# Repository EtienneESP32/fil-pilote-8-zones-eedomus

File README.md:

# Contrôleur fil pilote 8 zones — eedomus / ESP32-S3

Projet de carte rail DIN destinée à piloter huit zones de chauffage par fil pilote, avec intégration locale eedomus par HTTP. La carte contrôleur retenue pour l'étude est le Waveshare ESP32-S3-POE-ETH, SKU 28771, avec option d'alimentation PoE et alimentation secteur isolée locale.

> **Attention — projet en cours de conception.** Le PCB EasyEDA généré par conversion est un brouillon non placé/routé et ne doit pas être commandé ou raccordé au secteur. Le schéma source contient encore l'ancienne architecture WT32-S1/MCP23017. Les distances d'isolement, les valeurs de composants, la topologie triphasée, le codage des six ordres et les protections ne sont pas validés. Toute réalisation secteur doit être revue par une personne qualifiée.

## État

- Cahier initial, PDF et JSON EasyEDA source archivés dans le dépôt.
- Dossier de documentation technique dans [`docs/`](docs/README.md).
- Copie de travail EasyEDA R1 créée dans le compte EasyEDA de l'utilisateur, distincte du projet source.
- PCB issu de conversion présent dans cette copie R1; placement, contour, routage, DRC et export de fabrication restent à faire.
- Le projet vise 8 sorties fil pilote, 6 ordres, phase `PHASE_PROT` unique retenue par l'utilisateur, Ethernet, eedomus et options PoE/alimentation locale.
- Une recherche de projets similaires met en évidence un conflit à résoudre : un projet triphasé comparable exige une phase pilote correspondant à la phase d'alimentation du radiateur.

## Documentation

- [Index de la documentation](docs/README.md)
- [Cahier des charges](docs/01_Cahier-des-charges.md)
- [Architecture et interfaces](docs/02_Architecture-et-interfaces.md)
- [Nomenclature prévisionnelle](docs/03_Nomenclature.md)
- [Note d'implantation PCB](docs/04_Implantation-PCB.md)
- [Firmware et exploitation](docs/05_Firmware-et-exploitation.md)
- [Plan de validation](docs/06_Plan-de-validation.md)
- [Questions/décisions ouvertes](docs/07_Questions-a-confirmer.md)
- [Revue du schéma source](docs/08_Revue-schema-source.md)
- [Commande directe des optos](docs/09_Commande-directe-opto.md)
- [Projets similaires](docs/10_Projets-similaires.md)

## Contenu source

- `contour du projet.docx` : cahier initial.
- `SCH_FilPilote_8Zones_DIN_2_2026-11-06.json` : export EasyEDA source, ancienne version.
- `Schematic_FilPilote_8Zones_DIN_2_2026-11-06.pdf` : export PDF de cette source, obsolète par rapport aux choix R1.
- `Analyse et commentaires.md` : revue initiale et décisions ultérieures.

## Sauvegarde GitHub

La publication distante n'est pas encore effectuée. Recommandation : créer un dépôt **privé** au départ, vérifier les fichiers inclus et ne le rendre public qu'après revue sécurité/documentation. Voir [`GITHUB_PUBLISHING.md`](GITHUB_PUBLISHING.md).

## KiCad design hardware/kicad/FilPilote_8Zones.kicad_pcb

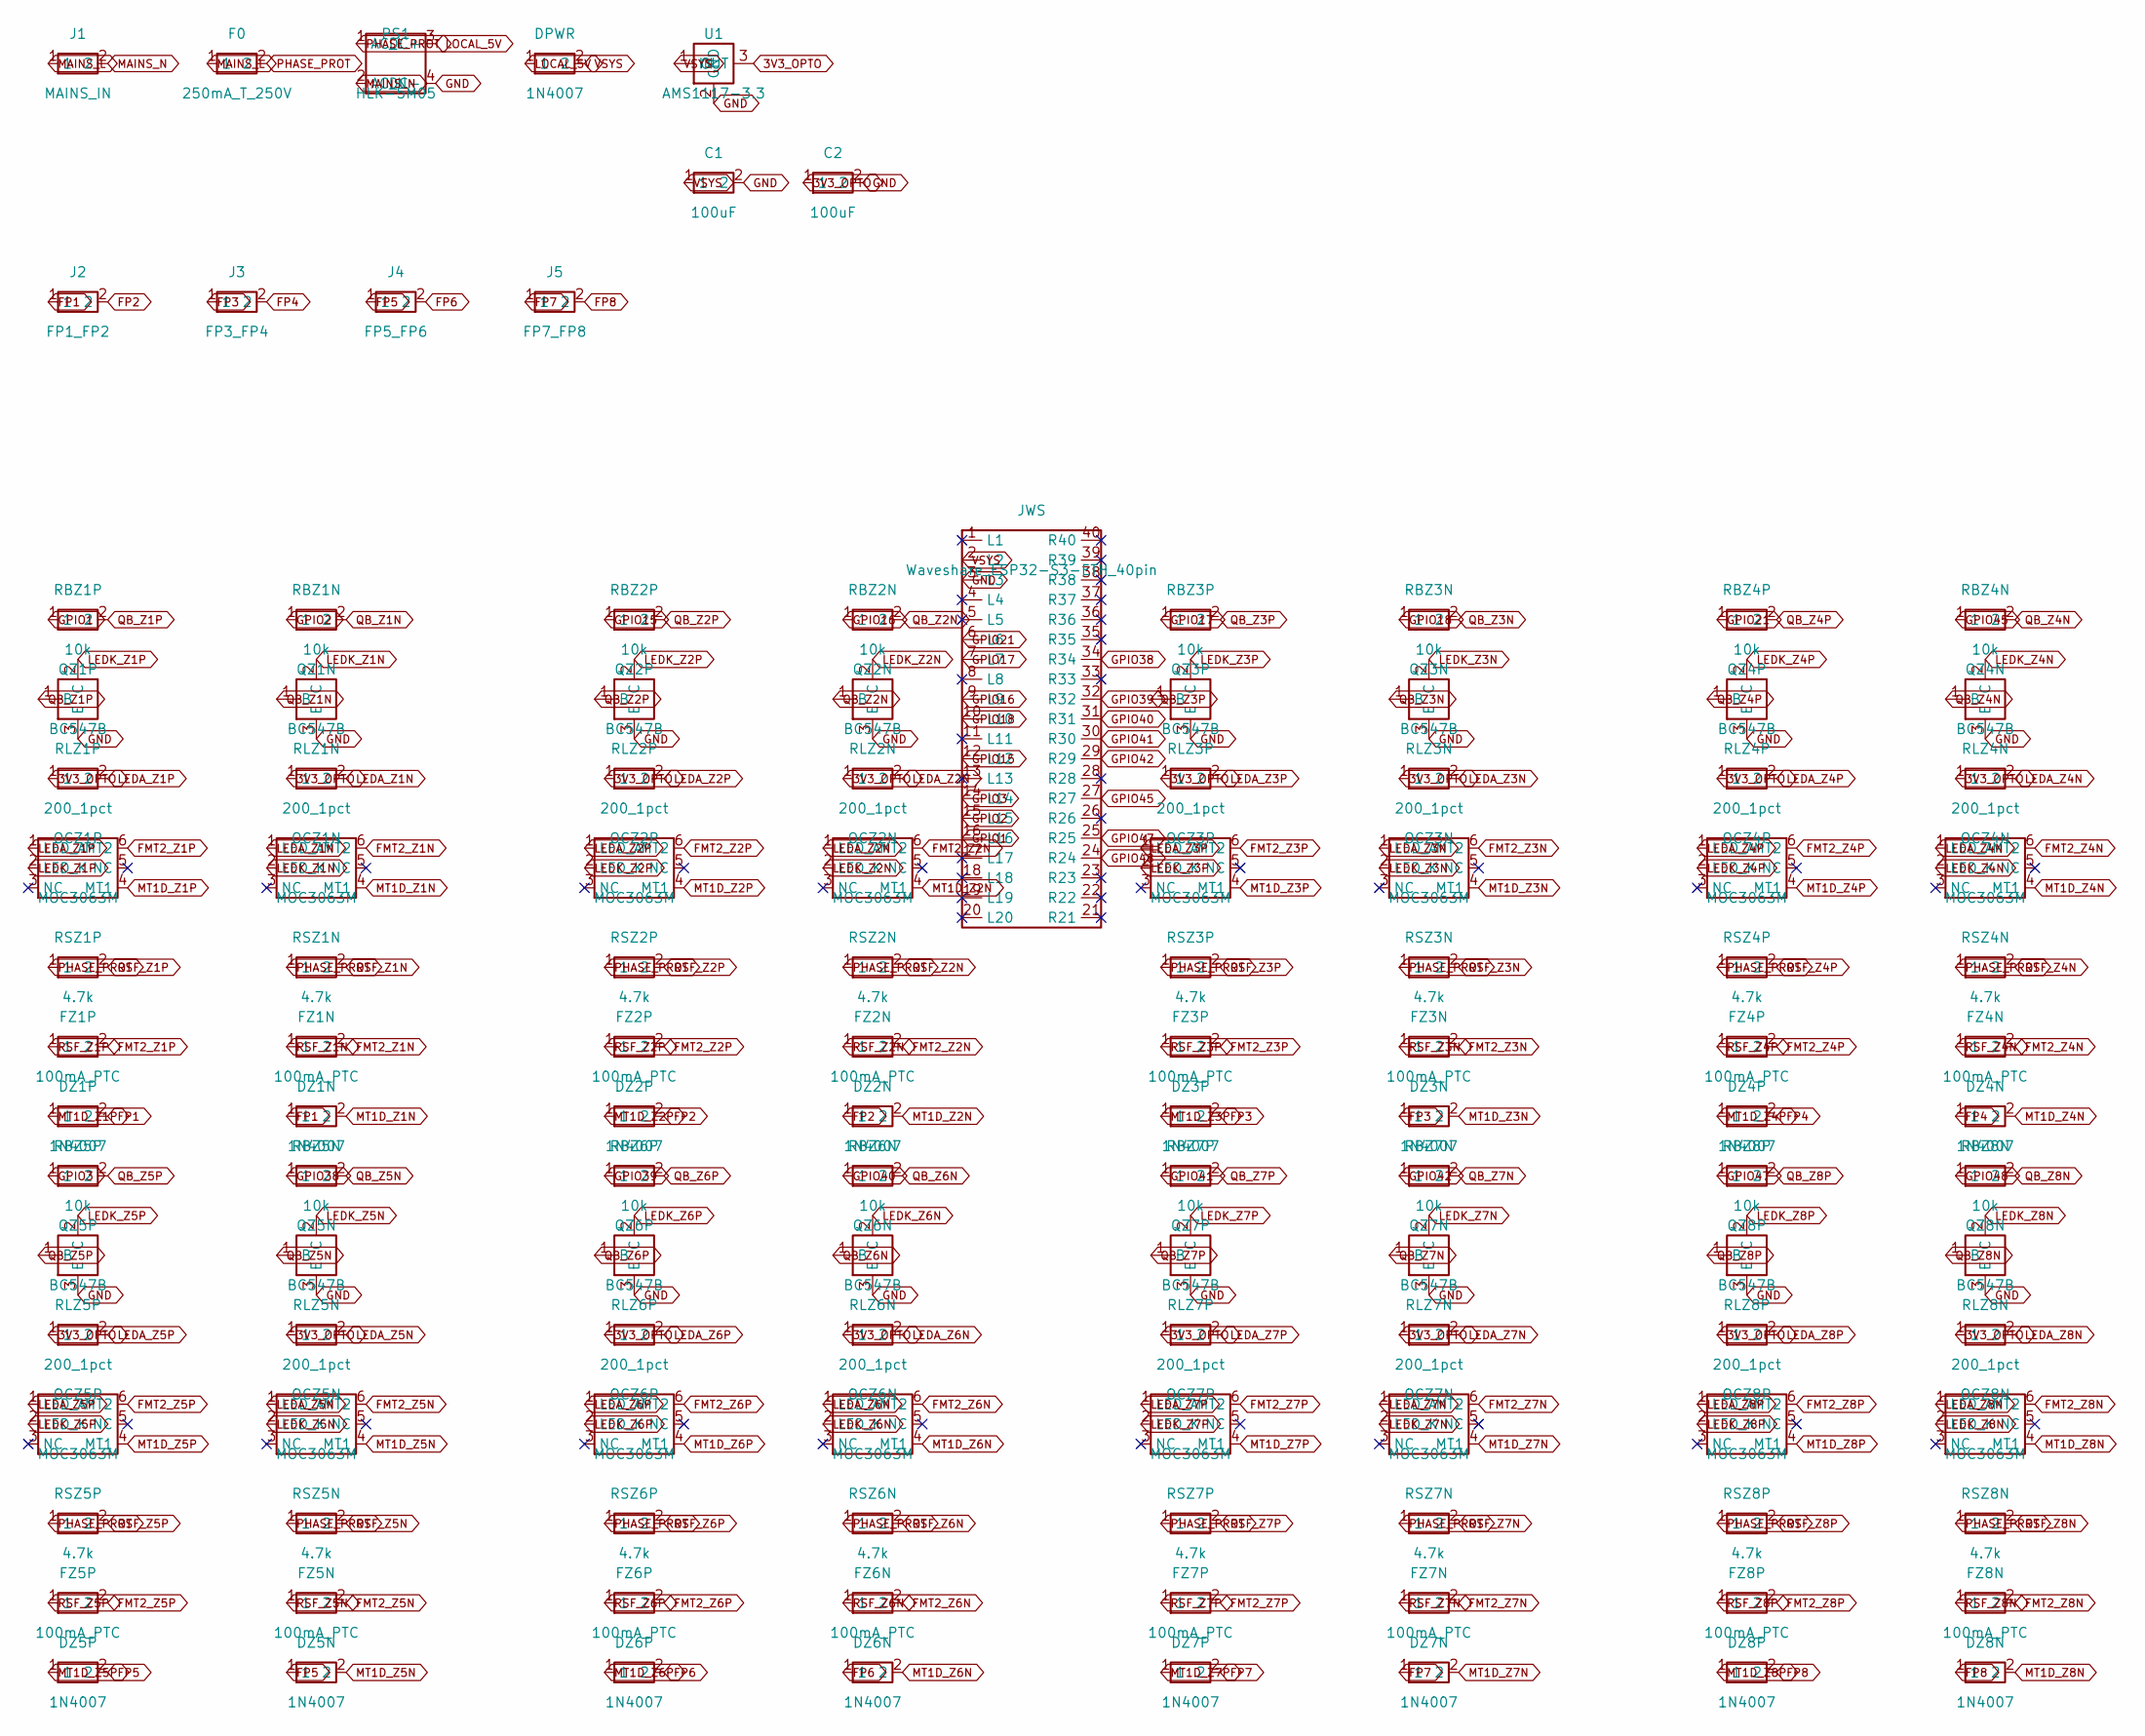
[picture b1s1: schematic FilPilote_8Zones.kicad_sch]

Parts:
C1, C2: 100uF; CAP_THT_Radial
DPWR: 1N4007; DO41_THT
DZ1N, DZ1P, DZ2N, DZ2P, DZ3N, DZ3P, DZ4N, DZ4P, DZ5N, DZ5P, DZ6N, DZ6P, DZ7N, DZ7P, DZ8N, DZ8P: 1N4007; DO41_THT
F0: 250mA_T_250V; Axial_THT
FZ1N, FZ1P, FZ2N, FZ2P, FZ3N, FZ3P, FZ4N, FZ4P, FZ5N, FZ5P, FZ6N, FZ6P, FZ7N, FZ7P, FZ8N, FZ8P: 100mA_PTC; Axial_THT
J1: MAINS_IN; TerminalBlock_2.54_2pin
J2: FP1_FP2; TerminalBlock_5.08_2pin
J3: FP3_FP4; TerminalBlock_5.08_2pin
J4: FP5_FP6; TerminalBlock_5.08_2pin
J5: FP7_FP8; TerminalBlock_5.08_2pin
JWS: Waveshare_ESP32-S3-ETH_40pin; PinHeader_2x20_2.54_Pico
OCZ1N, OCZ1P, OCZ2N, OCZ2P, OCZ3N, OCZ3P, OCZ4N, OCZ4P, OCZ5N, OCZ5P, OCZ6N, OCZ6P, OCZ7N, OCZ7P, OCZ8N, OCZ8P: MOC3063M; DIP6_THT
PS1: HLK-5M05; Module_PSU4
QZ1N, QZ1P, QZ2N, QZ2P, QZ3N, QZ3P, QZ4N, QZ4P, QZ5N, QZ5P, QZ6N, QZ6P, QZ7N, QZ7P, QZ8N, QZ8P: BC547B; TO92_BEC
RBZ1N, RBZ1P, RBZ2N, RBZ2P, RBZ3N, RBZ3P, RBZ4N, RBZ4P, RBZ5N, RBZ5P, RBZ6N, RBZ6P, RBZ7N, RBZ7P, RBZ8N, RBZ8P: 10k; Axial_THT
RLZ1N, RLZ1P, RLZ2N, RLZ2P, RLZ3N, RLZ3P, RLZ4N, RLZ4P, RLZ5N, RLZ5P, RLZ6N, RLZ6P, RLZ7N, RLZ7P, RLZ8N, RLZ8P: 200_1pct; Axial_THT
RSZ1N, RSZ1P, RSZ2N, RSZ2P, RSZ3N, RSZ3P, RSZ4N, RSZ4P, RSZ5N, RSZ5P, RSZ6N, RSZ6P, RSZ7N, RSZ7P, RSZ8N, RSZ8P: 4.7k; Axial_THT
U1: AMS1117-3.3; TO220_3pin

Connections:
3V3_OPTO: C2.1, RLZ1N.1, RLZ1P.1, RLZ2N.1, RLZ2P.1, RLZ3N.1, RLZ3P.1, RLZ4N.1, RLZ4P.1, RLZ5N.1, RLZ5P.1, RLZ6N.1, RLZ6P.1, RLZ7N.1, RLZ7P.1, RLZ8N.1, RLZ8P.1, U1.3 (OUT); also elsewhere on the board
FMT2_Z1N: FZ1N.2, OCZ1N.6 (MT2)
FMT2_Z1P: FZ1P.2, OCZ1P.6 (MT2)
FMT2_Z2N: FZ2N.2, OCZ2N.6 (MT2)
FMT2_Z2P: FZ2P.2, OCZ2P.6 (MT2)
FMT2_Z3N: FZ3N.2, OCZ3N.6 (MT2)
FMT2_Z3P: FZ3P.2, OCZ3P.6 (MT2)
FMT2_Z4N: FZ4N.2, OCZ4N.6 (MT2)
FMT2_Z4P: FZ4P.2, OCZ4P.6 (MT2)
FMT2_Z5N: FZ5N.2, OCZ5N.6 (MT2)
FMT2_Z5P: FZ5P.2, OCZ5P.6 (MT2)
FMT2_Z6N: FZ6N.2, OCZ6N.6 (MT2)
FMT2_Z6P: FZ6P.2, OCZ6P.6 (MT2)
FMT2_Z7N: FZ7N.2, OCZ7N.6 (MT2)
FMT2_Z7P: FZ7P.2, OCZ7P.6 (MT2)
FMT2_Z8N: FZ8N.2, OCZ8N.6 (MT2)
FMT2_Z8P: FZ8P.2, OCZ8P.6 (MT2)
FP1: DZ1N.1, DZ1P.2, J2.1; also elsewhere on the board
FP2: DZ2N.1, DZ2P.2, J2.2; also elsewhere on the board
FP3: DZ3N.1, DZ3P.2, J3.1; also elsewhere on the board
FP4: DZ4N.1, DZ4P.2, J3.2; also elsewhere on the board
FP5: DZ5N.1, DZ5P.2, J4.1
FP6: DZ6N.1, DZ6P.2, J4.2
FP7: DZ7N.1, DZ7P.2, J5.1
FP8: DZ8N.1, DZ8P.2, J5.2
GND: C1.2, C2.2, JWS.3 (L3), PS1.4 (DC-), QZ1N.3 (E), QZ1P.3 (E), QZ2N.3 (E), QZ2P.3 (E), QZ3N.3 (E), QZ3P.3 (E), QZ4N.3 (E), QZ4P.3 (E), QZ5N.3 (E), QZ5P.3 (E), QZ6N.3 (E), QZ6P.3 (E), QZ7N.3 (E), QZ7P.3 (E), QZ8N.3 (E), QZ8P.3 (E), U1.2 (GND)
GPIO1: JWS.16 (L16), RBZ1P.1
GPIO2: JWS.15 (L15), RBZ1N.1
GPIO3: JWS.14 (L14), RBZ5P.1
GPIO15: JWS.12 (L12), RBZ2P.1
GPIO16: JWS.9 (L9), RBZ2N.1
GPIO17: JWS.7 (L7), RBZ3P.1
GPIO18: JWS.10 (L10), RBZ3N.1
GPIO21: JWS.6 (L6), RBZ4P.1
GPIO38: JWS.34 (R34), RBZ5N.1
GPIO39: JWS.32 (R32), RBZ6P.1
GPIO40: JWS.31 (R31), RBZ6N.1; also elsewhere on the board
GPIO41: JWS.30 (R30), RBZ7P.1
GPIO42: JWS.29 (R29), RBZ7N.1
GPIO45: JWS.27 (R27), RBZ4N.1
GPIO47: JWS.25 (R25), RBZ8P.1
GPIO48: JWS.24 (R24), RBZ8N.1
LEDA_Z1N: OCZ1N.1 (LED_A), RLZ1N.2
LEDA_Z1P: OCZ1P.1 (LED_A), RLZ1P.2
LEDA_Z2N: OCZ2N.1 (LED_A), RLZ2N.2
LEDA_Z2P: OCZ2P.1 (LED_A), RLZ2P.2
LEDA_Z3N: OCZ3N.1 (LED_A), RLZ3N.2
LEDA_Z3P: OCZ3P.1 (LED_A), RLZ3P.2
LEDA_Z4N: OCZ4N.1 (LED_A), RLZ4N.2
LEDA_Z4P: OCZ4P.1 (LED_A), RLZ4P.2
LEDA_Z5N: OCZ5N.1 (LED_A), RLZ5N.2
LEDA_Z5P: OCZ5P.1 (LED_A), RLZ5P.2
LEDA_Z6N: OCZ6N.1 (LED_A), RLZ6N.2
LEDA_Z6P: OCZ6P.1 (LED_A), RLZ6P.2
LEDA_Z7N: OCZ7N.1 (LED_A), RLZ7N.2
LEDA_Z7P: OCZ7P.1 (LED_A), RLZ7P.2
LEDA_Z8N: OCZ8N.1 (LED_A), RLZ8N.2
LEDA_Z8P: OCZ8P.1 (LED_A), RLZ8P.2
LEDK_Z1N: OCZ1N.2 (LED_K), QZ1N.2 (C)
LEDK_Z1P: OCZ1P.2 (LED_K), QZ1P.2 (C)
LEDK_Z2N: OCZ2N.2 (LED_K), QZ2N.2 (C)
LEDK_Z2P: OCZ2P.2 (LED_K), QZ2P.2 (C)
LEDK_Z3N: OCZ3N.2 (LED_K), QZ3N.2 (C)
LEDK_Z3P: OCZ3P.2 (LED_K), QZ3P.2 (C)
LEDK_Z4N: OCZ4N.2 (LED_K), QZ4N.2 (C)
LEDK_Z4P: OCZ4P.2 (LED_K), QZ4P.2 (C)
LEDK_Z5N: OCZ5N.2 (LED_K), QZ5N.2 (C)
LEDK_Z5P: OCZ5P.2 (LED_K), QZ5P.2 (C)
LEDK_Z6N: OCZ6N.2 (LED_K), QZ6N.2 (C)
LEDK_Z6P: OCZ6P.2 (LED_K), QZ6P.2 (C)
LEDK_Z7N: OCZ7N.2 (LED_K), QZ7N.2 (C)
LEDK_Z7P: OCZ7P.2 (LED_K), QZ7P.2 (C)
LEDK_Z8N: OCZ8N.2 (LED_K), QZ8N.2 (C)
LEDK_Z8P: OCZ8P.2 (LED_K), QZ8P.2 (C)
LOCAL_5V: DPWR.1, PS1.3 (DC+); also elsewhere on the board
MAINS_L: F0.1, J1.1
MAINS_N: J1.2, PS1.2 (AC_N)
MT1D_Z1N: DZ1N.2, OCZ1N.4 (MT1)
MT1D_Z1P: DZ1P.1, OCZ1P.4 (MT1)
MT1D_Z2N: DZ2N.2, OCZ2N.4 (MT1)
MT1D_Z2P: DZ2P.1, OCZ2P.4 (MT1); also elsewhere on the board
MT1D_Z3N: DZ3N.2, OCZ3N.4 (MT1)
MT1D_Z3P: DZ3P.1, OCZ3P.4 (MT1); also elsewhere on the board
MT1D_Z4N: DZ4N.2, OCZ4N.4 (MT1)
MT1D_Z4P: DZ4P.1, OCZ4P.4 (MT1); also elsewhere on the board
MT1D_Z5N: DZ5N.2, OCZ5N.4 (MT1)
MT1D_Z5P: DZ5P.1, OCZ5P.4 (MT1)
MT1D_Z6N: DZ6N.2, OCZ6N.4 (MT1)
MT1D_Z6P: DZ6P.1, OCZ6P.4 (MT1)
MT1D_Z7N: DZ7N.2, OCZ7N.4 (MT1); also elsewhere on the board
MT1D_Z7P: DZ7P.1, OCZ7P.4 (MT1)
MT1D_Z8N: DZ8N.2, OCZ8N.4 (MT1); also elsewhere on the board
MT1D_Z8P: DZ8P.1, OCZ8P.4 (MT1); also elsewhere on the board
PHASE_PROT: F0.2, PS1.1 (AC_L), RSZ1N.1, RSZ1P.1, RSZ2N.1, RSZ2P.1, RSZ3N.1, RSZ3P.1, RSZ4N.1, RSZ4P.1, RSZ5N.1, RSZ5P.1, RSZ6N.1, RSZ6P.1, RSZ7N.1, RSZ7P.1, RSZ8N.1, RSZ8P.1
QB_Z1N: QZ1N.1 (B), RBZ1N.2
QB_Z1P: QZ1P.1 (B), RBZ1P.2
QB_Z2N: QZ2N.1 (B), RBZ2N.2
QB_Z2P: QZ2P.1 (B), RBZ2P.2
QB_Z3N: QZ3N.1 (B), RBZ3N.2
QB_Z3P: QZ3P.1 (B), RBZ3P.2
QB_Z4N: QZ4N.1 (B), RBZ4N.2
QB_Z4P: QZ4P.1 (B), RBZ4P.2
QB_Z5N: QZ5N.1 (B), RBZ5N.2
QB_Z5P: QZ5P.1 (B), RBZ5P.2
QB_Z6N: QZ6N.1 (B), RBZ6N.2
QB_Z6P: QZ6P.1 (B), RBZ6P.2
QB_Z7N: QZ7N.1 (B), RBZ7N.2
QB_Z7P: QZ7P.1 (B), RBZ7P.2
QB_Z8N: QZ8N.1 (B), RBZ8N.2
QB_Z8P: QZ8P.1 (B), RBZ8P.2
RSF_Z1N: FZ1N.1, RSZ1N.2
RSF_Z1P: FZ1P.1, RSZ1P.2
RSF_Z2N: FZ2N.1, RSZ2N.2
RSF_Z2P: FZ2P.1, RSZ2P.2
RSF_Z3N: FZ3N.1, RSZ3N.2
RSF_Z3P: FZ3P.1, RSZ3P.2
RSF_Z4N: FZ4N.1, RSZ4N.2
RSF_Z4P: FZ4P.1, RSZ4P.2
RSF_Z5N: FZ5N.1, RSZ5N.2
RSF_Z5P: FZ5P.1, RSZ5P.2
RSF_Z6N: FZ6N.1, RSZ6N.2
RSF_Z6P: FZ6P.1, RSZ6P.2
RSF_Z7N: FZ7N.1, RSZ7N.2
RSF_Z7P: FZ7P.1, RSZ7P.2
RSF_Z8N: FZ8N.1, RSZ8N.2
RSF_Z8P: FZ8P.1, RSZ8P.2
VSYS: C1.1, DPWR.2, JWS.2 (L2), U1.1 (IN)

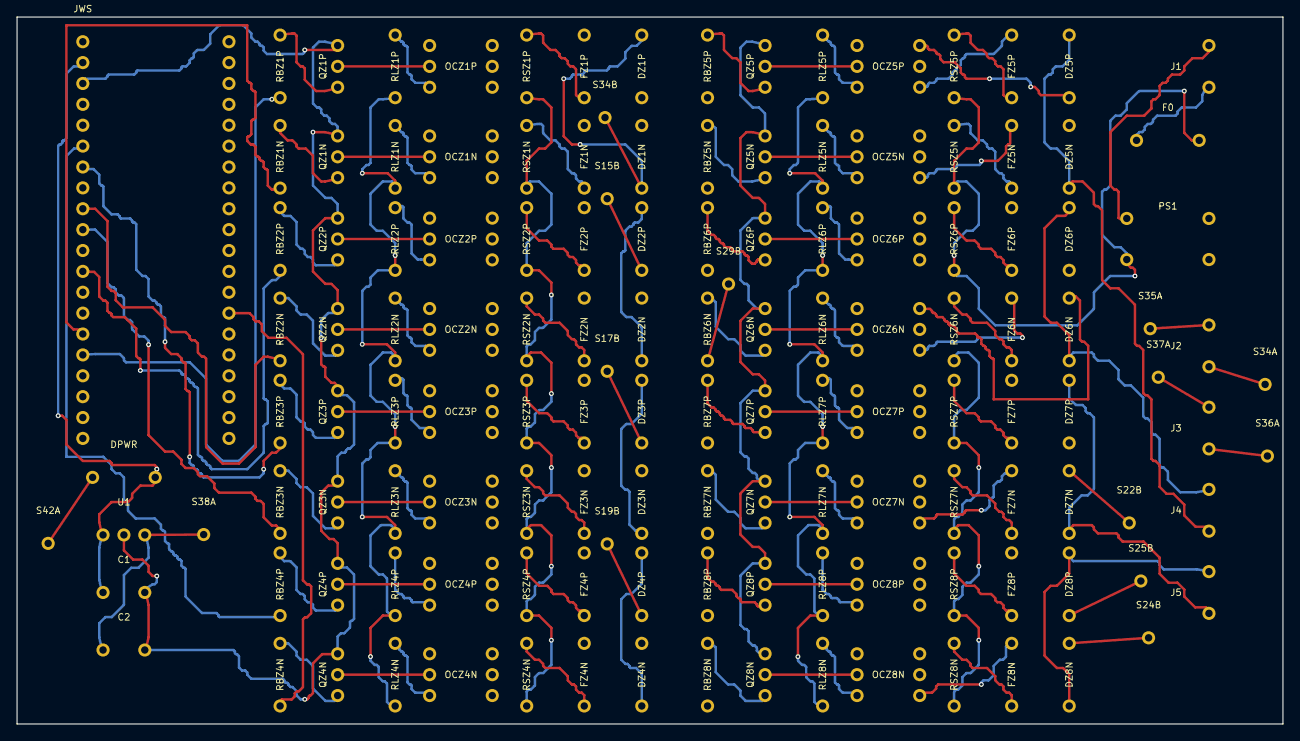
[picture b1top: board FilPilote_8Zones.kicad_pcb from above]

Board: 2 copper layers, 154.0 x 86.0 mm, 138 parts (0 on the bottom side), 127 nets.

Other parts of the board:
S15B, S17B, S19B, S22B, S24B, S25B, S29B, S34A, S34B, S35A, S36A, S37A, S38A, S42A: strap; ANCHOR1

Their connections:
3V3_OPTO: S38A.1; also elsewhere on the board
FP1: S34A.1, S34B.1; also elsewhere on the board
FP2: S35A.1; also elsewhere on the board
FP3: S36A.1; also elsewhere on the board
FP4: S37A.1; also elsewhere on the board
GPIO40: S29B.1; also elsewhere on the board
LOCAL_5V: S42A.1; also elsewhere on the board
MT1D_Z2P: S15B.1; also elsewhere on the board
MT1D_Z3P: S17B.1; also elsewhere on the board
MT1D_Z4P: S19B.1; also elsewhere on the board
MT1D_Z7N: S22B.1; also elsewhere on the board
MT1D_Z8N: S24B.1; also elsewhere on the board
MT1D_Z8P: S25B.1; also elsewhere on the board
